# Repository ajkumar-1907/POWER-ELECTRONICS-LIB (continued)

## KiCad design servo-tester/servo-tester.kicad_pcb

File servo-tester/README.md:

# Servo Tester (NE555)

A standalone servo tester built around an NE555 timer. It generates the PWM control pulse a hobby servo expects, and turning the potentiometer sweeps the servo through its range. No microcontroller or code is needed.

## Overview

Hobby servos (SG90, MG995, etc.) set their shaft angle from the **width of a repeating pulse**: about 1 ms for one end, 1.5 ms for centre and 2 ms for the other end. This board makes that pulse with a 555 in astable mode. A steering diode separates the charge and discharge paths, so the pulse width (high time) and the gap between pulses (low time) can be set independently. That lets the board produce a short pulse with a long gap, which a plain 555 astable can't do.

## Working Principle

1. **Charging (output HIGH):** C1 charges from VCC through R2 + RV1 and diode D1, which bypasses R1. This sets the **pulse width**, and turning RV1 changes it.
2. **Discharging (output LOW):** when C1 reaches ⅔ VCC, the 555's discharge pin (7) pulls low. C1 discharges through R1 (3.3 MΩ) only, because D1 is now reverse-biased. This sets the **gap between pulses**.
3. **Output:** pin 3 (Q) drives the servo's signal line on J2. J2 also passes VCC and GND through to power the servo.
4. **Indicator:** D2 lights through R3 (1 kΩ) whenever the board is powered.

## Key Equations

**Pulse width (output HIGH, set by RV1):**
```
t_high = 0.693 × (R2 + RV1) × C1
       = 0.693 × (56k … 156k) × 22 nF ≈ 0.85 ms … 2.4 ms
```

**Gap between pulses (output LOW):**
```
t_low = 0.693 × R1 × C1 = 0.693 × 3.3 MΩ × 22 nF ≈ 50 ms
```

**Frame period and frequency:**
```
T = t_high + t_low ≈ 51–53 ms   →   f ≈ 19 Hz
```

**Indicator LED current (6 V supply):**
```
I_LED = (VCC − V_LED) / R3 ≈ (6 − 2) / 1k ≈ 4 mA
```

## Typical Applications

- Bench-testing servos before fitting them in an RC model or robot
- Centring a servo horn during assembly
- Checking a servo for jitter, dead band or stripped gears
- Driving a servo manually with no Arduino or receiver

## Specifications (this design)

| Parameter | Value |
|---|---|
| Supply Voltage | 6 V DC (4.8–6 V servo range; NE555 accepts 4.5–16 V) |
| Pulse Width | ≈ 0.85 ms to 2.4 ms, adjustable with RV1 |
| Frame Rate | ≈ 19 Hz (≈ 52 ms period) |
| Output | 3-pin servo header: GND / VCC / SIG |
| Board Size | 30.5 × 27.75 mm, 2-layer, 4 × mounting holes |

## Bill of Materials

| Ref | Value | Package | Qty |
|---|---|---|---|
| U1 | NE555P timer | DIP-8 | 1 |
| RV1 | 100 kΩ potentiometer | Alps RK163, single | 1 |
| R1 | 3.3 MΩ, ¼ W | Axial DIN0204 | 1 |
| R2 | 56 kΩ, ¼ W | Axial DIN0204 | 1 |
| R3 | 1 kΩ, ¼ W | Axial DIN0204 | 1 |
| C1 | 22 nF ceramic | Disc, P5 mm | 1 |
| D1 | 1N4148 | DO-35 | 1 |
| D2 | 3 mm LED | THT | 1 |
| J1 | 2-pin header (power in) | 2.54 mm | 1 |
| J2 | 3-pin header (servo) | 2.54 mm | 1 |

## Design Notes

- **The pulse range is wider than standard.** The standard range is 1–2 ms, but this board goes from about 0.85 ms to 2.4 ms. At the ends of the pot's travel, some servos will push against their mechanical end stops and buzz. To trim the range to about 0.9–2.1 ms, change R2 to 62 kΩ and RV1 to 50 kΩ, or reduce C1.
- **The frame rate is lower than standard.** About 19 Hz is slower than the usual 50 Hz (20 ms period). Most analog servos don't mind, but some digital servos may jitter or lose holding torque. To get about 50 Hz, change R1 to 1.2 MΩ (t_low ≈ 18 ms).
- **Supply.** The servo takes its power from J1 through J2. Use a supply that can deliver the servo's stall current, which is often 0.5–1 A or more. Don't power it from a microcontroller's 5 V pin.

## Pros & Cons

**Pros:**
- Simple, cheap and code-free; all through-hole parts
- Pulse width and frame rate are set independently (diode steering)
- Small enough to keep in a toolbox

**Cons:**
- Pulse width drifts with temperature and component tolerance (it is an RC timer)
- Manual control only: no auto-sweep or centre-detent mode
- The pot's end positions overshoot the standard 1–2 ms range (see Design Notes)

## Files in This Folder

| File | Description |
|---|---|
| `servo-tester.kicad_pro` | KiCad project file |
| `servo-tester.kicad_sch` | Schematic source file |
| `servo-tester.kicad_pcb` | PCB layout source file |
| `servo-tester-PTH.drl` | Plated through-hole drill file |
| `servo-tester-NPTH.drl` | Non-plated through-hole drill file |
| `gerbers/` | Gerber files for fabrication |
| `schematic.png` | Schematic preview image |
| `pcb-layout2.png` | PCB layout preview (KiCad editor view) |
| `pcb-layout.png` | PCB top and bottom render from the Gerbers |

## How to Use

1. Clone or download this repository.
2. Open `servo-tester.kicad_pro` in [KiCad](https://www.kicad.org/) (v10 or later).
3. To manufacture, zip the contents of `gerbers/` together with the two `.drl` files and upload them to any PCB fab.
4. After assembly, connect a 6 V supply to J1 (observe the + / − marking) and the servo to J2 (GND / VCC / SIG). Then turn RV1 to sweep the servo.

## License

Released under the [MIT License](../LICENSE).

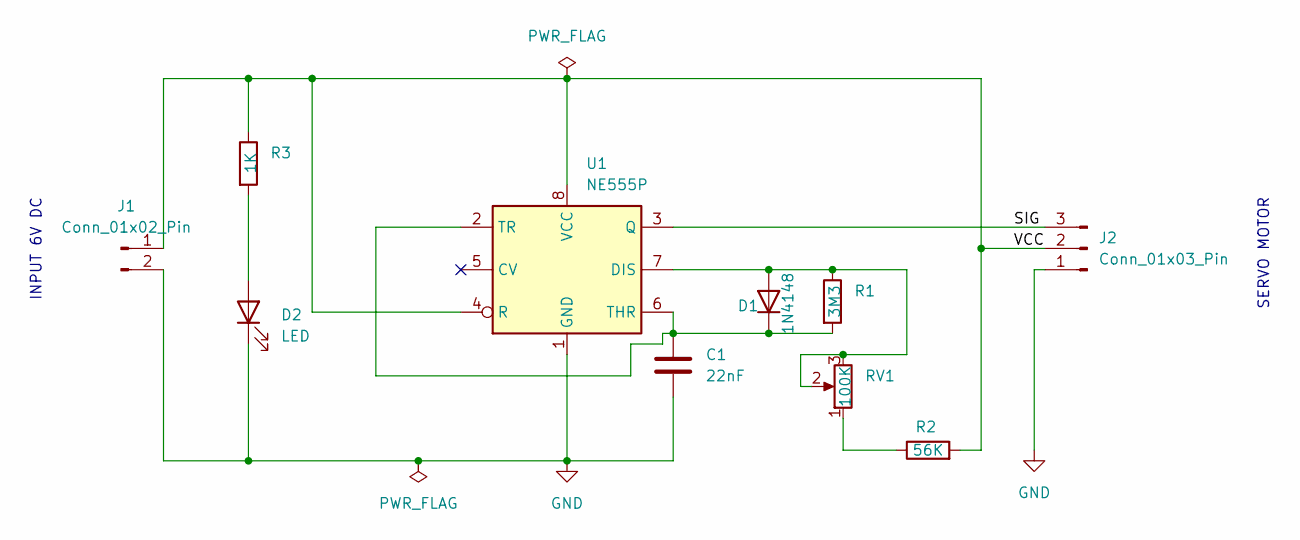
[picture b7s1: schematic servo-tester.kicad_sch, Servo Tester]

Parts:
C1: 22nF; C_Disc_D4.3mm_W1.9mm_P5.00mm
D1: 1N4148; D_DO-35_SOD27_P7.62mm_Horizontal
D2: LED; LED_D3.0mm
J1: Conn_01x02_Pin; PinHeader_1x02_P2.54mm_Horizontal
J2: Conn_01x03_Pin; PinHeader_1x03_P2.54mm_Horizontal
R1: 3M3; R_Axial_DIN0204_L3.6mm_D1.6mm_P7.62mm_Horizontal
R2: 56K; R_Axial_DIN0204_L3.6mm_D1.6mm_P7.62mm_Horizontal
R3: 1K; R_Axial_DIN0204_L3.6mm_D1.6mm_P7.62mm_Horizontal
RV1: 100K; Potentiometer_Alps_RK163_Single_Horizontal
U1: NE555P; DIP-8_W7.62mm

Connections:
/SIG: J2.3, U1.3 (Q)
/VCC: J1.1, J2.2, R2.2, R3.1, U1.4 (R), U1.8 (VCC)
GND: C1.2, D2.1 (K), J1.2, J2.1, U1.1 (GND)
unnamed: D1.2 (A), R1.1, RV1.2, RV1.3, U1.7 (DIS)
unnamed: C1.1, D1.1 (K), R1.2, U1.2 (TR), U1.6 (THR)
unnamed: D2.2 (A), R3.2
unnamed: R2.1, RV1.1

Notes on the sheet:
SERVO MOTOR
INPUT 6V DC

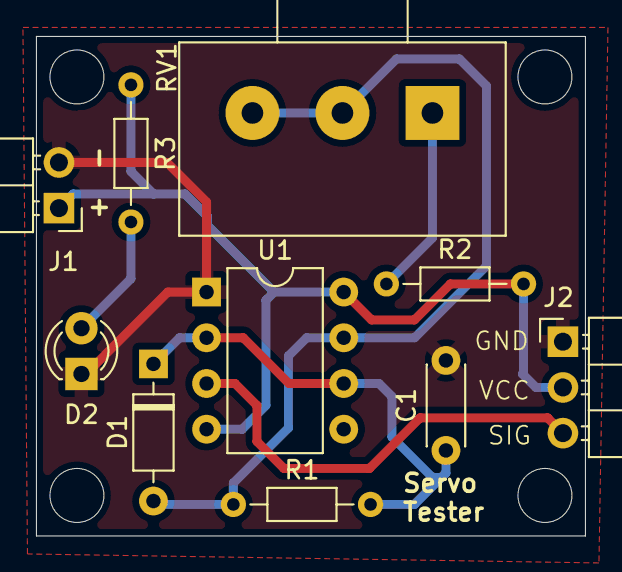
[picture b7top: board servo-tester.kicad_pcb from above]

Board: 2 copper layers, 30.5 x 27.8 mm, 10 parts (0 on the bottom side), 7 nets.

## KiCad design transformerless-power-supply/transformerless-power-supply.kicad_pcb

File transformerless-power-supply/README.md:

# Transformerless Power Supply (Capacitive Dropper)

An AC-DC power supply that produces a **regulated 5 V DC** output directly from **230 V AC mains** without a transformer. A high-voltage X-rated capacitor drops the voltage, a bridge rectifier converts it to DC, and an LM7805 regulates the output.

> ⚠️ **DANGER — mains voltage, no isolation.** Every point on this board, **including the 5 V output and GND**, can be at lethal mains potential. Never touch the board while it's plugged in, never connect it to a grounded device (PC, oscilloscope, USB), and only build it if you know how to work safely with mains.

## Overview

Transformerless (capacitive dropper) supplies are used where cost and size matter more than isolation: smart plugs, LED bulbs, small appliance controllers and energy meters. Instead of stepping the voltage down with a transformer, a capacitor in series with the mains limits the **current**. Because a capacitor's reactance dissipates almost no real power, this dropper stays cool, unlike a resistive dropper.

## Working Principle

1. **Current limiting:** C4 (2.2 µF, code "225") is in series with the mains live line. Its reactance at 50 Hz limits the current to about 150 mA. R3 (1 MΩ) is a bleeder that discharges C4 once the supply is unplugged.
2. **Rectification:** D1–D4 (1N4007) form a full-wave bridge.
3. **Filtering:** C2 (1000 µF) is the bulk reservoir capacitor, and C1 (0.1 µF) bypasses high-frequency noise.
4. **Voltage clamping:** zener diodes D5 and D6 are meant to hold the rectified rail at a safe level for the regulator. (See [Design Notes](#design-notes).)
5. **Regulation:** U1 (LM7805) regulates the rail to 5 V, and C3 (470 µF) stabilises the output.
6. **Indicator:** D7 lights through R4 (2.2 kΩ) when the rail is up.

## Key Equations

**Dropper capacitor reactance:**
```
Xc = 1 / (2π × f × C) = 1 / (2π × 50 × 2.2 µF) ≈ 1.45 kΩ
```

**Maximum available current (Vrail ≪ Vmains):**
```
I ≈ Vmains / Xc = 230 / 1447 ≈ 159 mA (RMS)
```
The dropper acts as a **current source**: the board must always sink this current, either through the load or through the zener clamp.

**Sizing C4 for a required current:**
```
C = I / (2π × f × Vmains)
```

**Bleeder discharge (R3 × C4):**
```
τ = 1 MΩ × 2.2 µF = 2.2 s
P(R3) = 230² / 1 MΩ ≈ 53 mW
```

**Regulator dissipation:**
```
P(U1) = (Vrail − 5 V) × I_load
```

## Typical Applications

- Smart plugs, Wi-Fi switches and IoT relays (powering a microcontroller from mains)
- LED bulbs and drivers
- Energy meters, timers and small appliance control boards
- Any sealed, low-current (< 100 mA) device where isolation isn't required

## Specifications (this design)

| Parameter | Value |
|---|---|
| Input Voltage | 230 V AC, 50 Hz (mains, direct) |
| Output Voltage | 5 V DC regulated (LM7805) |
| Output Current | ≤ 100 mA recommended (dropper limit ≈ 150 mA total) |
| Isolation | **None** |
| Board Size | 48.75 × 37.5 mm, 2-layer, 4 × mounting holes |

## Bill of Materials

| Ref | Value | Package | Qty |
|---|---|---|---|
| C4 | 2.2 µF (225K) **X2-rated, ≥ 275 V AC** polypropylene | Rect. 18 × 6 mm, P15 mm | 1 |
| R3 | 1 MΩ, ¼ W | Axial DIN0207 | 1 |
| D1–D4 | 1N4007 | DO-41 | 4 |
| C1 | 0.1 µF ceramic | Disc, P5 mm | 1 |
| C2 | 1000 µF electrolytic (≥ 25 V) | Radial D10 mm, P5 mm | 1 |
| D5, D6 | Zener diode (see Design Notes) | DO-41 / A-405 | 2 |
| R1, R2 | 20 kΩ, ¼ W | Axial DIN0207 | 2 |
| R4 | 2.2 kΩ, ¼ W | Axial DIN0207 | 1 |
| D7 | 5 mm LED | THT | 1 |
| U1 | LM7805 | TO-220 | 1 |
| C3 | 470 µF electrolytic (≥ 10 V) | Radial D10 mm, P3.8 mm | 1 |
| J1, J2 | 2-pin screw terminal, 5.08 mm | THT | 2 |

## Design Notes

These are known issues with the current revision, recorded so that anyone building it doesn't get caught out:

- **The zener clamp is ineffective.** Each zener (D5, D6) is in series with a 20 kΩ resistor, so the two branches together can only sink about 1 mA. The dropper delivers about 150 mA, and with a light load or none, the voltage on C2 will rise towards the mains peak (~325 V). That exceeds the LM7805's 35 V input limit and C2's voltage rating. **Fix:** put one 1 W zener (12–15 V) directly across C2, with no series resistor, so it can absorb the full dropper current.
- **No input protection.** The production checklist for capacitive droppers is:
  - a fuse in series with the live line
  - a ~100 Ω, 1 W surge-limiting resistor in series with C4 to limit inrush at switch-on
  - a MOV across the input to absorb mains spikes
- **Component ratings.** C4 **must** be an X2 safety capacitor, because an ordinary film capacitor can fail short-circuit across the mains. C2's voltage rating must be above the zener voltage.
- **Current budget.** The available current is fixed by C4. The load, the LED, the regulator's quiescent current and the zener all share it. Increase C4 if you need more output current.

## Pros & Cons

**Pros:**
- Very small, light and cheap; no transformer
- The capacitive dropper dissipates almost no power
- Simple through-hole design

**Cons:**
- **No galvanic isolation**: a shock hazard, and unsafe for any user-accessible output
- Output current is fixed and small (tens of mA)
- Poor efficiency at light load, because the zener burns the excess current
- Sensitive to mains surges and frequency (50 vs 60 Hz changes the current)

## Files in This Folder

| File | Description |
|---|---|
| `transformerless-power-supply.kicad_pro` | KiCad project file |
| `transformerless-power-supply.kicad_sch` | Schematic source file |
| `transformerless-power-supply.kicad_pcb` | PCB layout source file |
| `transformerless-power-supply-PTH.drl` | Plated through-hole drill file |
| `transformerless-power-supply-NPTH.drl` | Non-plated through-hole drill file |
| `gerbers/` | Gerber files for fabrication |
| `schematic.png` | Schematic preview image |
| `pcb-layout2.png` | PCB layout preview (KiCad editor view) |
| `pcb-layout.png` | PCB top and bottom render from the Gerbers |

## How to Use

1. Clone or download this repository.
2. Open `transformerless-power-supply.kicad_pro` in [KiCad](https://www.kicad.org/) (v10 or later).
3. Apply the fixes in [Design Notes](#design-notes) before ordering boards.
4. To manufacture, zip the contents of `gerbers/` together with the two `.drl` files and upload them to any PCB fab.
5. Test it for the first time through an isolation transformer, or a series bulb limiter, never straight from the wall socket.

## License

Released under the [MIT License](../LICENSE).

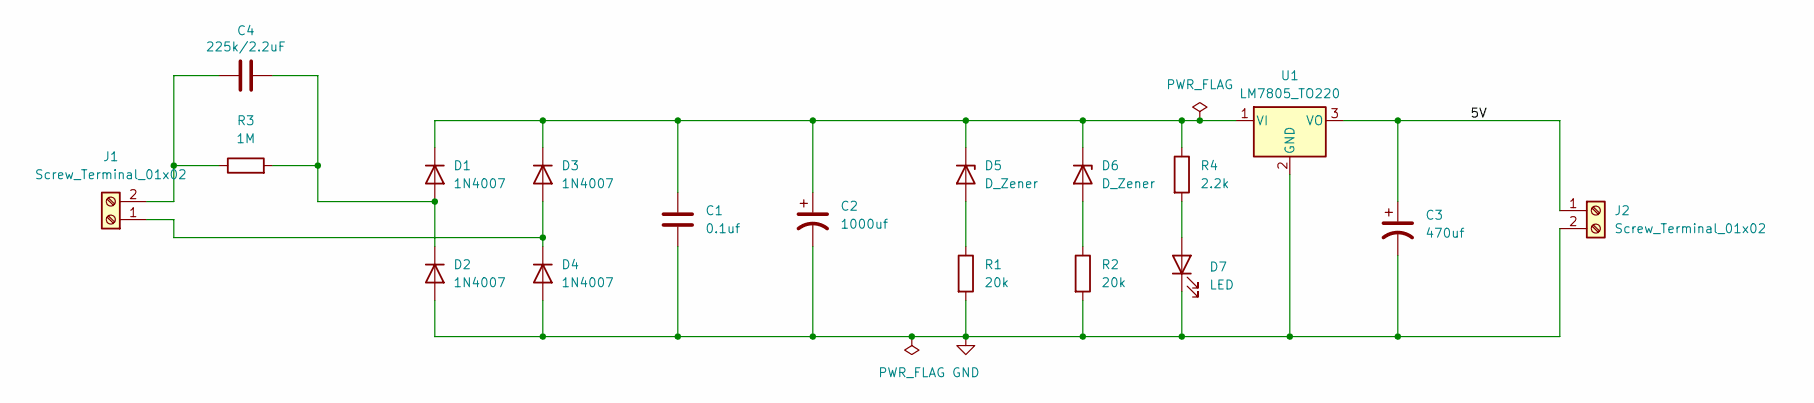
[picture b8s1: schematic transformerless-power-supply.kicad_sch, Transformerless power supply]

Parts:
C1: 0.1uf; C_Disc_D4.7mm_W2.5mm_P5.00mm
C2: 1000uf; CP_Radial_D10.0mm_P5.00mm
C3: 470uf; CP_Radial_D10.0mm_P3.80mm
C4: 225k/2.2uF; C_Rect_L18.0mm_W6.0mm_P15.00mm_FKS3_FKP3
D1, D2, D3, D4: 1N4007; D_DO-41_SOD81_P10.16mm_Horizontal
D5, D6: D_Zener; D_A-405_P7.62mm_Horizontal
D7: LED; LED_D5.0mm
J1, J2: Screw_Terminal_01x02; TerminalBlock_bornier-2_P5.08mm
R1, R2: 20k; R_Axial_DIN0207_L6.3mm_D2.5mm_P7.62mm_Horizontal
R3: 1M; R_Axial_DIN0207_L6.3mm_D2.5mm_P7.62mm_Horizontal
R4: 2.2k; R_Axial_DIN0207_L6.3mm_D2.5mm_P7.62mm_Horizontal
U1: LM7805_TO220; TO-220-3_Vertical

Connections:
/5V: C3.1, J2.1, U1.3 (VO)
GND: C1.2, C2.2, C3.2, D2.2 (A), D4.2 (A), D7.1 (K), J2.2, R1.2, R2.2, U1.2 (GND)
unnamed: C4.2, D1.2 (A), D2.1 (K), R3.2
unnamed: C1.1, C2.1, D1.1 (K), D3.1 (K), D5.1 (K), D6.1 (K), R4.1, U1.1 (VI)
unnamed: D3.2 (A), D4.1 (K), J1.1
unnamed: D5.2 (A), R1.1
unnamed: D6.2 (A), R2.1
unnamed: D7.2 (A), R4.2
unnamed: C4.1, J1.2, R3.1

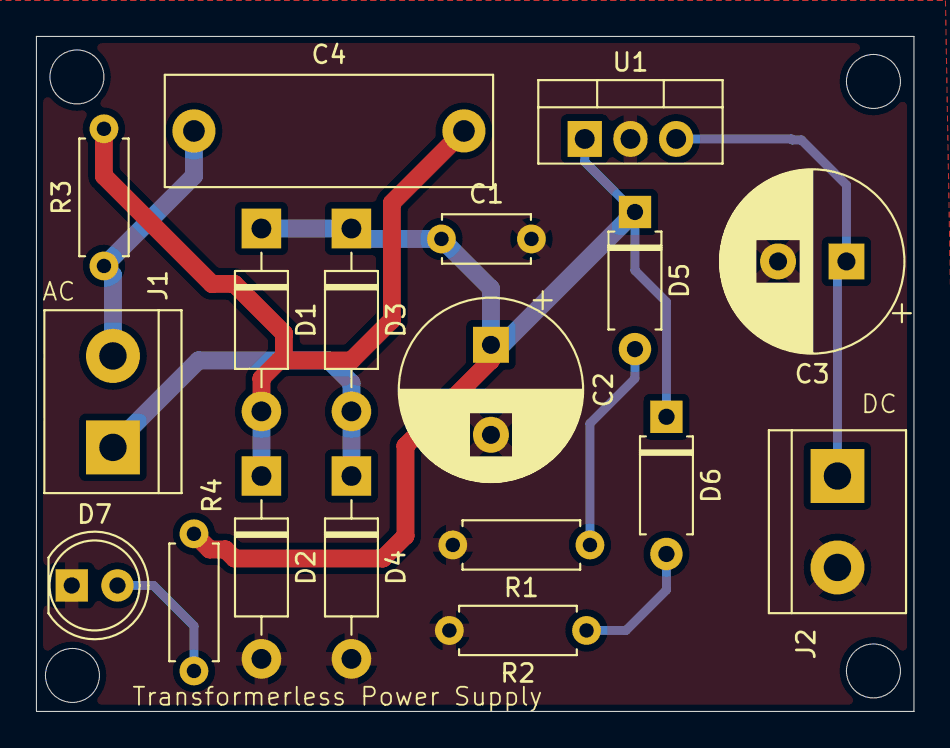
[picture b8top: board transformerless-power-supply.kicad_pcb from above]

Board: 2 copper layers, 48.8 x 37.5 mm, 18 parts (0 on the bottom side), 9 nets.
